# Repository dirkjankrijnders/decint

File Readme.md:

Decoder interface
=================

A simple PCB to interface a microcontroller (or any other 5V logic) to either Loconet or track based signals such as DCC/Motorola/MFX/Selectrix. Interface knows nothing about the protocols. Note that the track signal can also come from the railsync lines on Loconet.

The interface can provide full opto-isolation from the track signal and provides 4 open collector opto-isolated feedback ports. Also it has a ACK generator for operating in DCC Service Mode.

The micro controller connection is primarily meant for mounting a Arduino Pro Mini or Pro Micro, but any connection can of course be made.

The board:
----------

The BOM
-------

| Reference                    |   | Value             | MFN                     | MFP          | S1PN    | S1PL                                                                                                                |
|------------------------------|---|-------------------|-------------------------|--------------|---------|---------------------------------------------------------------------------------------------------------------------|
| U102                         | 1 | 6N137             | FAIRCHILD SEMICONDUCTOR | 6N137SDM     | 2322504 | http://nl.farnell.com/fairchild-semiconductor/6n137sdm/opto-cplr-logic-gate-o-p-5kv-smd/dp/2322504                  |
| D101, D102                   | 2 | BAV199            | NXP                     | BAV99W,115   | 1081212 | http://nl.farnell.com/nxp/bav99w-115/diode-dual-0-15a-100v-sot-323/dp/1081212                                       |
| Q102                         | 1 | BC849             |                         |              |         |                                                                                                                     |
| Q101                         | 1 | BC857             |                         |              |         |                                                                                                                     |
| C101                         | 1 | CAP               |                         |              |         |                                                                                                                     |
| D104                         | 1 | 1N4148            |                         |              |         |                                                                                                                     |
| D103                         | 1 | D_Small           |                         |              |         |                                                                                                                     |
| U106                         | 1 | LM311N            | Texas Instruments      | LM311 |         |                                                                                                                     |
| U103                         | 1 | LTV-817           | LITEON | LTV-817S-V |         |                                                                                                                     |
| J104, J105                   | 2 | RJ12              | Lumberg                 | P 128        | 1243235 | http://nl.farnell.com/lumberg/p-128/modular-plug-crimp-rj12-6p6c/dp/1243235                                         |
| R101                         | 1 | 100               |                         |              |         |                                                                                                                     |
| R108                         | 1 | 10k               |                         |              |         |                                                                                                                     |
| R102                         | 1 | 1k5               |                         |              |         |                                                                                                                     |
| R103, R104, R105, R106, R107 | 5 | 1k                |                         |              |         |                                                                                                                     |
| R109                         | 1 | 4k7               |                         |              |         |                                                                                                                     |
| R110                         | 1 | 47k               |                         |              |         |                                                                                                                     |
| R112                         | 1 | 10k               |                         |              |         |                                                                                                                     |
| R111                         | 1 | 150k              |                         |              |         |                                                                                                                     |
| R113                         | 1 | 22k               |                         |              |         |                                                                                                                     |
| R114                         | 1 | 220k              |                         |              |         |                                                                                                                     |
| U101                         | 1 | OPTO-TRANSISTOR-4 | Vishay                  | TCMT4100     | 1779650 | http://nl.farnell.com/vishay/tcmt4100/optocplr-smd-16pin-4ch-trans-syst/dp/1779650                                  |
| U104                         | 1 | LM1117            | Texas Instruments       |LM1117MP-5.0               | 9778209 | http://nl.farnell.com/texas-instruments/lm1117mp-5-0/ldo-0-8a-5v-sot-223/dp/9778209?ost=9778209&selectedCategoryId= |

Note: The LM311 footprint on the PCB is meant for a DIP8-smd package, which doesn't really exist, bending the leads flat and soldering will work, in Rev.2 this will be a SOIC8 footprint.

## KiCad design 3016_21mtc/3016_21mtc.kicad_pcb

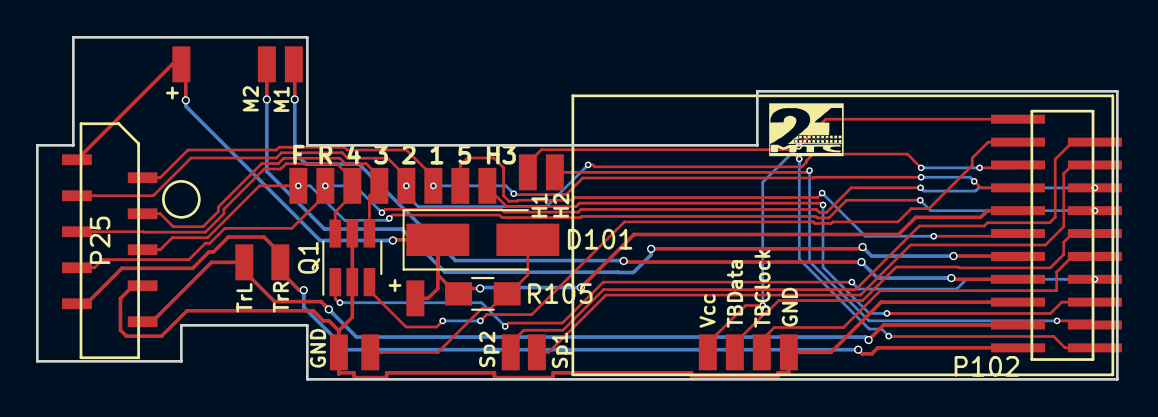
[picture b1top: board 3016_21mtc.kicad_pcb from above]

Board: 2 copper layers, 60.0 x 19.0 mm, 29 parts (0 on the bottom side), 24 nets.

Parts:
D101: S1G; D_SMA_Handsoldering
P1, P2, P3, P4, P5, P6, P7, P8, P9, P10, P11, P12, P13, P14, P15, P16, P17, P18, P19, P20, P21, P22, P23, P24: CONN_01X01; SMD_pad_01x02mm
P25: CONN_01X10; Molex_FPC-52808-1071_vertical
P102: CONN_02X11; Pin_Header_Straight_2x11_1.27_smd
Q1: FDC6303N; SOT-23-6_Handsoldering
R105: 100; R_0805_HandSoldering

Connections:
/Aux1: P21.1, P25.2, P102.16
/Aux2: P22.1, P25.3, P102.18
/Aux3: P15.1, P25.4, Q1.4
/Aux3_ttl: P102.20, Q1.3
/Aux4: P14.1, P25.5, Q1.6
/Aux4_ttl: P102.7, Q1.1
/Aux5: P23.1, P102.12
/F0_f_w: P9.1, P25.7, P102.15
/F0_r_y: P8.1, P25.6, P102.13
/Hall1: P4.1, P102.1
/Hall2: P5.1, P102.3
/Hall3: P6.1, P102.5
/Motor1: P19.1, P102.8
/Motor2: P20.1, P102.10
/Plus: D101.1, P2.1, P7.1, P25.1, P102.14, R105.2
/Speak1: P12.1, P102.17
/Speak2: P13.1, P102.19
/TBClock: P10.1, P102.9
/TBData: P11.1, P102.11
/TrackL: P18.1, P25.10, P102.4
/TrackR: P17.1, P25.9, P102.2
/Vcc: P24.1, P102.22
GND: P3.1, P16.1, P25.8, P102.6, Q1.2, Q1.5
unnamed: D101.2, P1.1, R105.1

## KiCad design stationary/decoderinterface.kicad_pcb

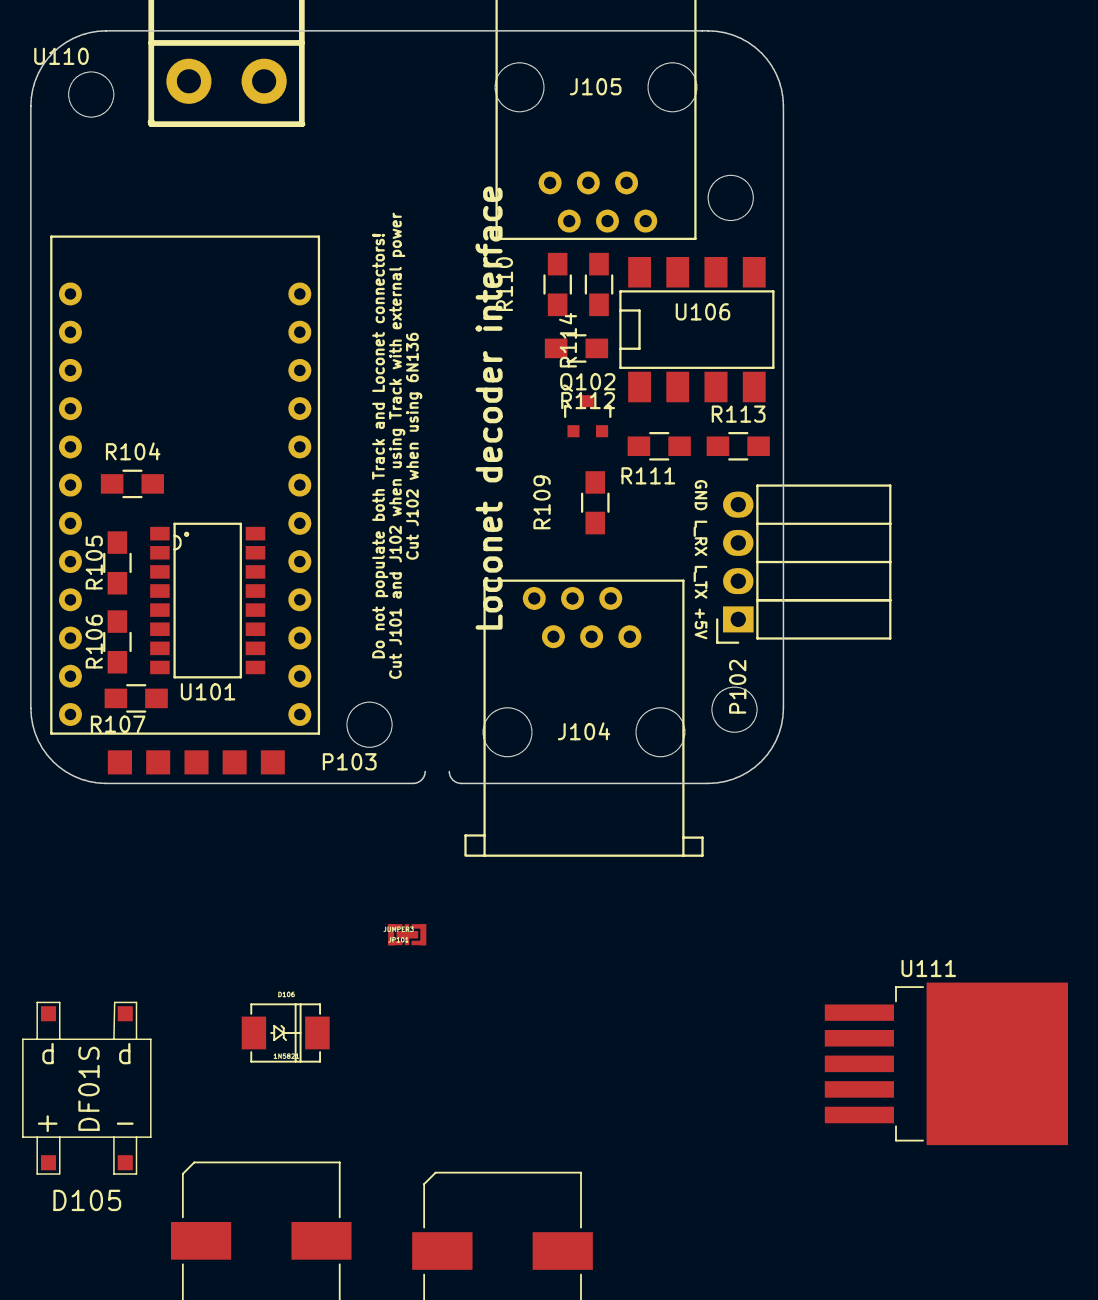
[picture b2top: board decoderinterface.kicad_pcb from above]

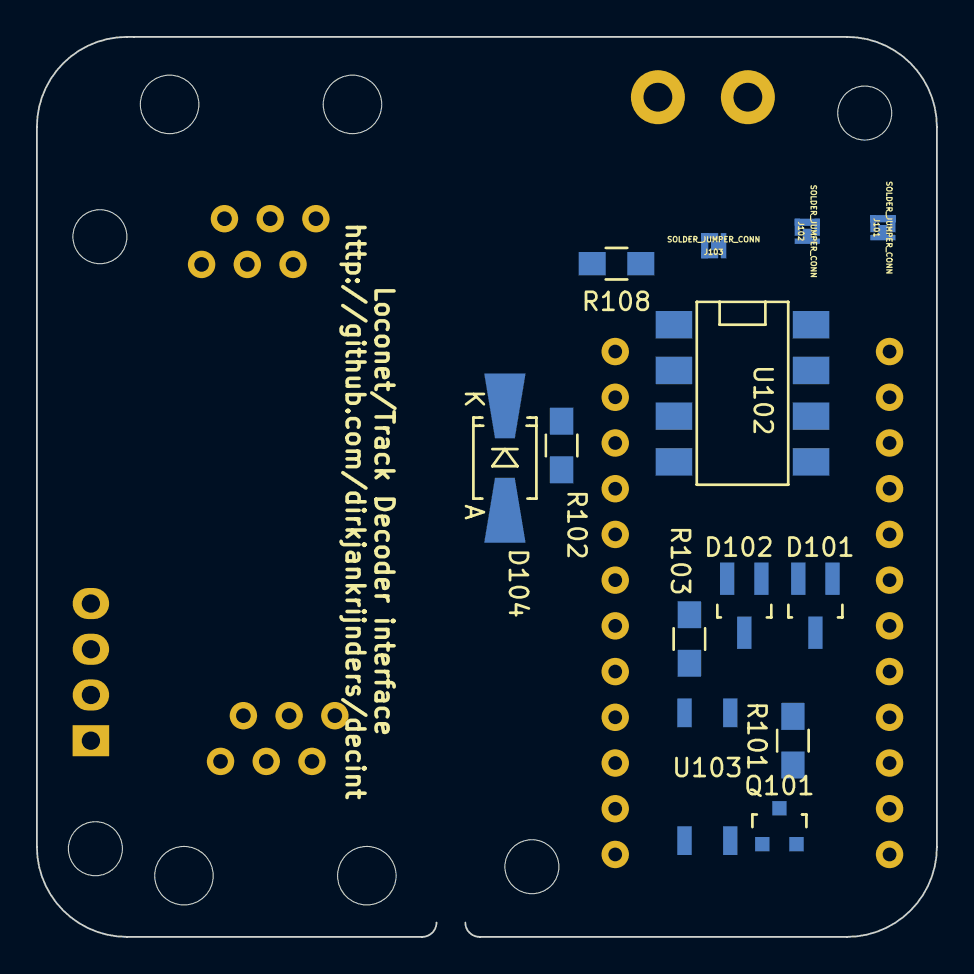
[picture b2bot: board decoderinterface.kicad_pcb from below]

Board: 2 copper layers, 50.0 x 50.0 mm, 42 parts (13 on the bottom side), 38 nets, no tracks yet.

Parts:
C102, C103: 330uF; CP_Elec_10x10
D101, D102: BAV199; SOT-23_Handsoldering
D104: 1N4148; Diode-Universal-SMA-SMB_Handsoldering
D105: DF01S; DIPSMD4
D106: 1N5821; DO-214AA
J101, J102, J103: SOLDER_JUMPER_CONN; SolderJumper
J104, J105: RJ12; RJ12_horizontal
JP101: JUMPER3; SolderJumper2way
P101: CONN_01X02; 2PIN_Screw_Block
P102: CONN_01X04; Socket_Strip_Angled_1x04
P103: CONN_01X05; SMD_PIN_01x05
Q101: BC857; SOT-23
Q102: BC849; SOT-23
R101: 100; R_0805_HandSoldering
R102: 1k5; R_0805_HandSoldering
R103, R104, R105, R106, R107: 1k; R_0805_HandSoldering
R108, R112: 10k; R_0805_HandSoldering
R109: 4k7; R_0805_HandSoldering
R110: 47k; R_0805_HandSoldering
R111: 150k; R_0805_HandSoldering
R113: 22k; R_0805_HandSoldering
R114: 220k; R_0805_HandSoldering
U101: OPTO-TRANSISTOR-4; HalfPitchMiniFlatPackage
U102: 6N137; DIP-8_SMD
U103: LTV-817; LTV_354
U105: Arduino_Pro_Micro
U106: LM311N; DIP-8_SMD
U107, U108, U109, U110: M3_Mounting_hole; MountingHole_3mm
U111: LM2575-5; TO-263-5Lead

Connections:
ACK: R103.1, U105.7
DC_GND: D105.2, J102.2
DC_PLUS: D105.4, J101.2
FB1: R104.1, U105.17
FB2: R105.1, U105.18
FB3: R106.1, U105.19
FB4: R107.1, U105.20
FBO1: P103.1, U101.16
FBO2: P103.2, U101.14
FBO3: P103.3, U101.12
FBO4: P103.4, U101.10
FBO_COMMON: P103.5, U101.9, U101.11, U101.13, U101.15
GND: C102.2, C103.2, D105.1, D106.2, J104.2, J104.5, J105.2, J105.5, P102.4, Q102.2, R111.2, R113.2, U101.2, U101.4, U101.6, U101.8, U102.5, U103.1, U105.9, U105.10, U105.14, U106.1, U106.4, U111.3, U111.5
Loconet: J104.3, J104.4, J105.3, J105.4, Q102.3, R110.1
Loconet_RX: JP101.2, P102.3, R114.1, U106.7
Loconet_TX: P102.2, R109.1, U105.5
unnamed: C102.1, D105.3, U111.1
unnamed: D101.1, D102.1, Q101.3, U103.3
unnamed: D101.3, D102.3, R101.2
unnamed: D104.1, R102.1, U102.2
unnamed: D106.1, U111.2
unnamed: J103.1, U102.7
unnamed: JP101.1, U105.2
unnamed: JP101.3, U105.6
unnamed: Q101.1, U103.4
unnamed: Q101.2, R101.1
unnamed: Q102.1, R109.2
unnamed: R103.2, U103.2
unnamed: R104.2, U101.1
unnamed: R105.2, U101.3
unnamed: R106.2, U101.5
unnamed: R107.2, U101.7
unnamed: R110.2, R111.1, R114.2, U106.2
unnamed: R112.2, R113.1, U106.3
Track_B: D102.2, D104.2, J102.1, J104.6, J105.6, P101.1, U102.3
Track_O: D101.2, J101.1, J104.1, J105.1, P101.2, R102.2
VCC: C103.1, J103.2, P102.1, R108.1, R112.1, U102.8, U105.16, U106.8, U111.4
tracksignal: R108.2, U102.6, U105.3

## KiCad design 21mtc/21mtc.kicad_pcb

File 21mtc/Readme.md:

This is a simple board to mount in a locomotive for interfacing to decoder. It supports both the 8-pin header connector (NMRA S-9.1.1, Medium connector) and the NEM660 version of the MTC21 connector, altough it is perfectly usable as a NMRA version, just the silkscreen is incorrect.

BOM
---

| Designator | value     | supplier | spl. no. | Description |
|------------|-----------|----------|----------|-------------|
| P102       |           |          |          | 0.05" pitch, 22 pin, SMD male header |
| R101, R104 |           |          |          | 1k, 0805 SMD Resistor |
| R102, R103 |           |          |          | 1k, 0805 SMD Resistor |
| Q101       | FDC6303N  | Farnell  | [1467964](http://nl.farnell.com/fairchild-semiconductor/fdc6303n/mosfet-dual-n-smd-supersot-6/dp/1467964)  | FAIRCHILD SEMICONDUCTOR  FDC6303N  Dual MOSFET, Dual N Channel, 680 mA, 25 V, 450 mohm, 4.5 V, 800 mV |
| R105       |           |          |          | 100 Ohm, 0805 SMD Resistor |
| D101       | S1G       | Farnell  | [2675039](http://nl.farnell.com/multicomp/s1g/rectifier-single-1a-400v-do-214ac/dp/2675039) | S1G, 1.0A SMD Diode |

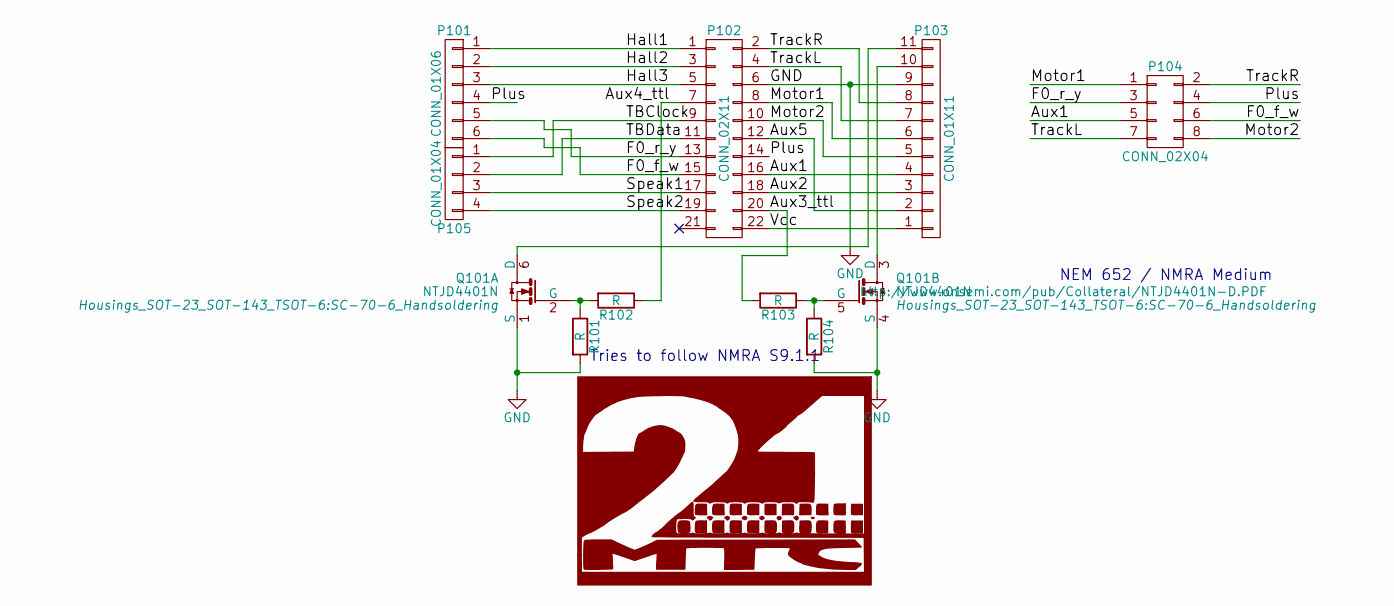
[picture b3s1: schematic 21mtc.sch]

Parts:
P101: CONN_01X06; solderpads_1x06_2mm
P102: CONN_02X11; Pin_Header_Straight_2x11_1.27_smd
P103: CONN_01X11; solderpads_1x11_2mm
P104: CONN_02X04; Pin_Header_Straight_2x04
P105: CONN_01X04; solderpads_1x04_2mm
Q101: NTJD4401N; SC-70-6_Handsoldering
R101, R102, R103, R104: R; R_0805_HandSoldering

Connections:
/Aux1: P102.16, P103.4, P104.5
/Aux2: P102.18, P103.3
/Aux3_ttl: P102.20, R103.2
/Aux4_ttl: P102.7, R102.1
/Aux5: P102.12, P103.2
/F0_f_w: P101.6, P102.15, P104.6
/F0_r_y: P101.5, P102.13, P104.3
/Hall1: P101.1, P102.1
/Hall2: P101.2, P102.3
/Hall3: P101.3, P102.5
/Motor1: P102.8, P103.6, P104.1
/Motor2: P102.10, P103.5, P104.8
/Plus: P101.4, P102.14, P104.4
/Speak1: P102.17, P105.3
/Speak2: P102.19, P105.4
/TBClock: P102.9, P105.1
/TBData: P102.11, P105.2
/TrackL: P102.4, P103.7, P104.7
/TrackR: P102.2, P103.8, P104.2
/Vcc: P102.22, P103.1
unnamed: P103.10, Q101.3 (D)
unnamed: Q101.2 (G), R101.1, R102.2
unnamed: Q101.5 (G), R103.1, R104.1

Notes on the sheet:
Tries to follow NMRA S9.1.1
NEM 652 / NMRA Medium

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
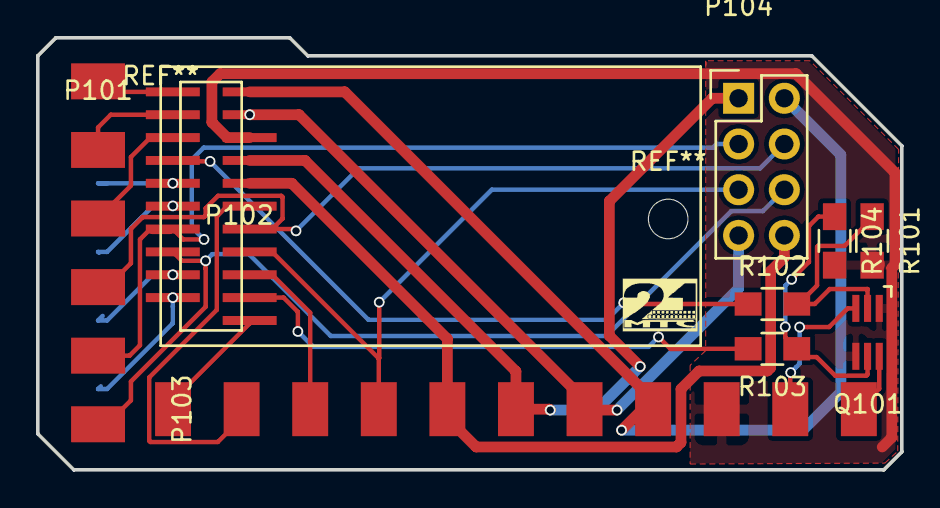
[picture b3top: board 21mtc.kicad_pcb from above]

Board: 2 copper layers, 48.0 x 24.0 mm, 10 parts (1 on the bottom side), 25 nets.

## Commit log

2015-11-20 First revision
2015-11-20 Start of documentation
2015-11-20 Fixed image link
2015-11-20 Really fixed the image
2015-11-20 added BOM
2015-11-20 Small update on BOM
2015-11-21 Better BOM
2015-11-21 Improved BOM information
2015-11-21 Small BOM information improvement
2015-11-22 Fix the RJ12 footprint in de BOM data
2015-12-14 Restructure directories
2015-12-14 Start 21MTC / NEM 652 system board
2015-12-15 Layout of a first draft
2016-05-01 MTC21 Updates
2016-05-01 Updated schematic with jumpers for ICP selection
2017-05-09 Silkscreen and track width fixes
2017-05-09 Made the design rule for power nets, track width 0.6mm
2017-05-12 Put the F0 pads on the front, moved the TB* pads to the back
2017-05-12 Library management
2017-05-12 Small cleanups
2017-06-13 First revision of 3016 board
2017-06-13 Added gerbers
2017-06-13 Added schematic and 3D render
2017-06-13 Switched to Protel gerber naming
2018-03-22 Fixed LM311 footprint and LM1117 symbol
